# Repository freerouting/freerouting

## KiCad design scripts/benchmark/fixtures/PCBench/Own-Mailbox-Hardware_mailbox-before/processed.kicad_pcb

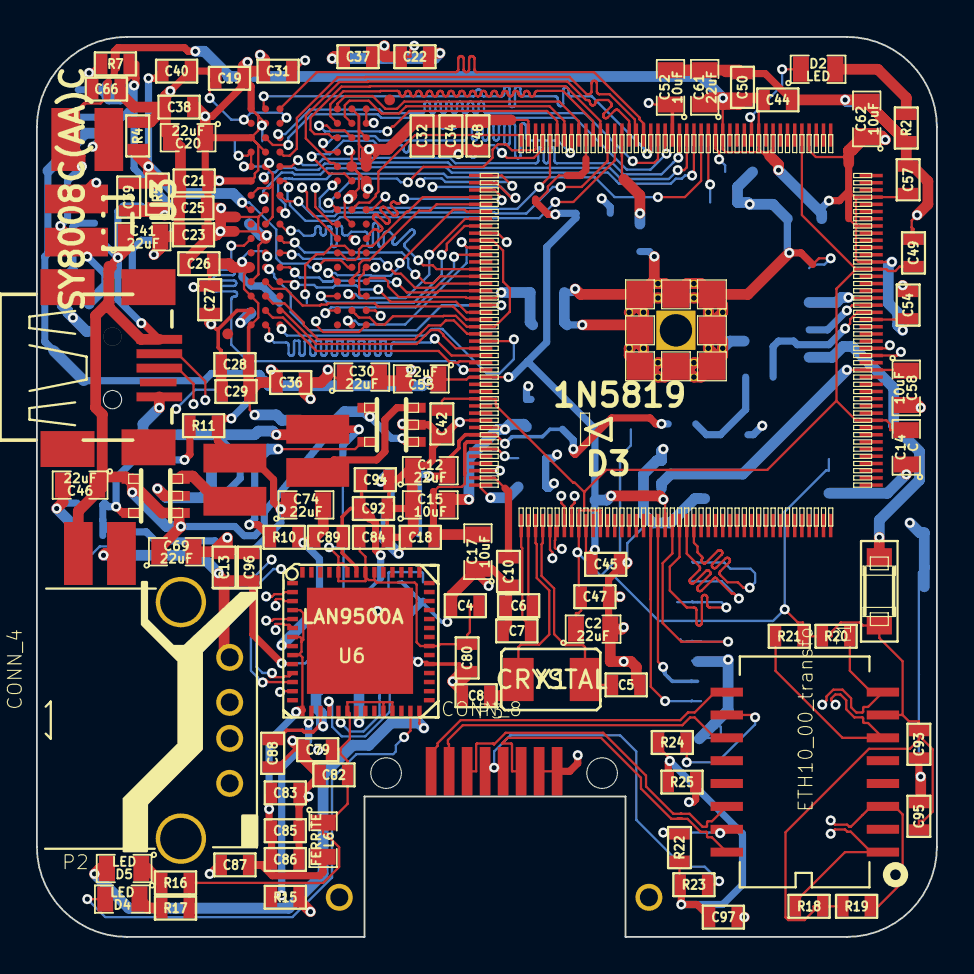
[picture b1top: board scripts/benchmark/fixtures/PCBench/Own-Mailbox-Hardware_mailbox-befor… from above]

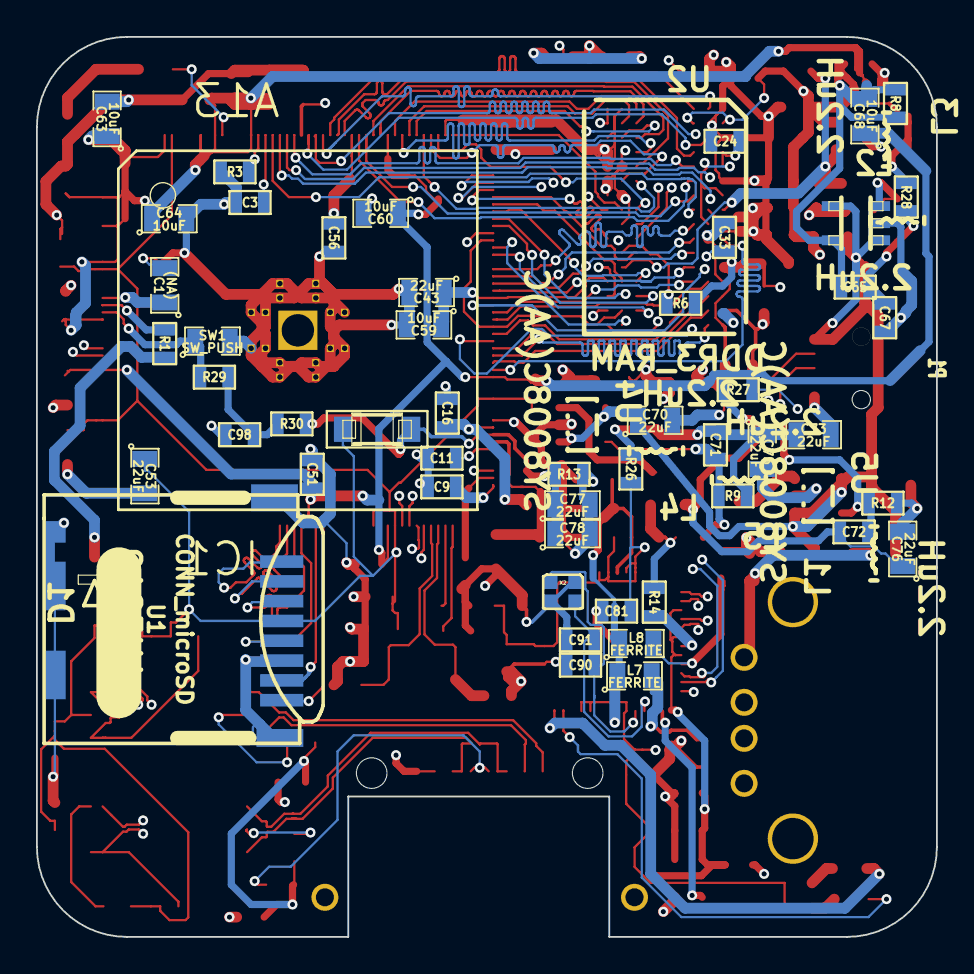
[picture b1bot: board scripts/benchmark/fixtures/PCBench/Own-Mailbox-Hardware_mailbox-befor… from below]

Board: 4 copper layers, 50.0 x 50.0 mm, 154 parts (50 on the bottom side), 74 nets.

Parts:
C1: (NA); SM0805
C2, C12, C20, C30, C41, C43, C46, C53, C55, C61, C69, C70, C73, C74, C75, C76, C77, C78: 22uF; SM0805
C3, C4, C13, C16, C18, C19, C21, C23, C24, C25, C26, C27, C28, C29, C31, C32, C33, C34, C36, C37, C38, C39, C40, C42, C44, C45, C47, C48, C49, C50, C51, C54, C56, C57, C79, C80, C81, C82, C83, C84, C85, C86, C87, C88, C92, C93, C94, C95, C96: 100nF; SM0603
C5, C8, C90, C91: 10pF; SM0603
C6, C7, C9, C10, C22, C98: 1nF; SM0603
C11, C89, C97: 1uF; SM0603
C14: C; SM0805
C15, C17, C52, C58, C59, C60, C62, C63, C64, C68: 10uF; SM0805
C65, C72: 22pF; SM0603
C66, C67: 22uF; SM0603
C71: 47pF; SM0603
D1, D3: 1N5819; SOD-123
D2, D4, D5: LED; SM0805
IC1: A13; TQFP176
L1, L2, L3, L4, L5: 2.2uH; CD32
L6, L7, L8: FERRITE; SM0805
P1: CONN_4; CONN_USB_MINI_PIERRE
P2: CONN_4; USB-A_TH
P3: CONN_8; RJ45_LP_RA_SMT
R1: 47k; SM0603
R2: 500R; SM0603
R3: 240R; SM0603
R4, R5: 1k(1%); SM0603
R6: 240R(1%); SM0603
R7: 2k(1%); SM0603
R8: 1.5k(1%); SM0603
R9: 100k(1%); SM0603
R10: 22k(1%); SM0603
R11: 4.99k(1%); SM0603
R12: 3.3k(1%); SM0603
R13: 2.2k; SM0603
R14, R15: R; SM0603
R16, R17: 100R; SM0603
R18, R19, R20, R21: 50R; SM0603
R22, R23, R24, R25: 75R; SM0603
R26, R27, R28: 0R; SM0603
R29: 6.8k(1%); SM0603
R30: 100k (1%); SM0603
SW1: SW_PUSH; SM0805
T1: ETH10_00_transfo; H1601CG
U1: CONN_microSD; Memory_Card_microSD_DM3CS-SF
U2: DDR3_RAM; FBGA96
U3, U4, U5: SY8008C(AA)C; SOT23-5
U6: LAN9500A; QFN48
X1: CRYSTAL; SMDXTAL24mhz
X2: CRYSTAL_SMD2; Xtal25Mhz

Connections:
1V5: C19.1, C20.1, C21.1, C23.1, C24.1, C25.1, C26.1, C27.1, C28.1, C29.1, C30.1, C31.1, C32.1, C33.1, C34.1, C36.1, C37.1, C38.1, C39.1, C43.1, C48.1, C52.1, C56.1, C59.1, IC1.23, IC1.30, IC1.43, IC1.53, IC1.62, R5.1, R27.1, U2.A1, U2.A8, U2.B2, U2.C1, U2.C9, U2.D2, U2.D9, U2.E9, U2.F1, U2.H2, U2.H9, U2.K2, U2.K8, U2.N1, U2.N9, U2.R1, U2.R9
3VA: C12.2, C77.1, C78.1, D3.2, IC1.81, R13.1, R30.1
+5V: C41.1, C46.1, C69.1, C70.1, L1.2, P1.1, U3.1, U3.4, U4.1, U4.4, U5.1, U5.4
/Erhernet/RX+: P3.7, T1.11
/Erhernet/RX-: P3.8, T1.9
/Erhernet/TX+: P3.3, T1.16
/Erhernet/TX-: P3.6, T1.14
LED1: D4.2, U6.27
LED2: D5.2, U6.28
unnamed: C1.1, IC1.159
unnamed: C3.1, IC1.18
unnamed: C6.2, IC1.90
unnamed: C7.2, IC1.89
unnamed: C9.2, IC1.88
unnamed: C10.2, IC1.87
unnamed: C11.2, IC1.83
unnamed: C13.1, L1.1, P2.1
unnamed: C15.2, C16.2, IC1.80
unnamed: C17.2, C18.2, IC1.82
unnamed: C22.2, IC1.86
unnamed: C39.2, C40.1, R4.1, R5.2, U2.H1, U2.M8
unnamed: C65.1, C66.1, C67.1, L2.2, R7.1, R28.2
unnamed: C71.1, C73.1, C75.1, L4.2, R9.1, R26.2
unnamed: C71.2, R9.2, R10.1, U4.5
unnamed: C72.1, C74.1, C76.1, L5.2, R11.1, R27.2
unnamed: C72.2, R11.2, R12.1, U5.5
unnamed: C90.2, U6.19, X2.3
unnamed: C91.2, U6.18, X2.1
unnamed: C97.2, R22.1, R23.1, R24.1, R25.1
unnamed: C98.1, R29.1, R30.2
unnamed: D1.2, R1.1
unnamed: D2.1, IC1.12
unnamed: D2.2, R2.1
unnamed: D4.1, R17.1
unnamed: D5.1, R16.1
unnamed: IC1.17, R3.1
unnamed: IC1.158, R1.2
unnamed: L2.1, U3.3
unnamed: L4.1, U4.3
unnamed: L5.1, U5.3
unnamed: P3.1, P3.2, R25.2
unnamed: P3.4, P3.5, R23.2
unnamed: R6.1, U2.L8
unnamed: R14.2, U6.8
unnamed: R15.2, U6.16
unnamed: R22.2, T1.15
unnamed: R24.2, T1.10
RPX_N: R20.1, T1.8, U6.5
RPX_P: R21.1, T1.6, U6.6
SDC0_CLK: IC1.110, U1.5
SDC0_CMD: IC1.111, U1.3
SDC0_D0: IC1.108, U1.7
SDC0_D1: IC1.107, U1.8
SDC0_D2: IC1.113, U1.1
SDC0_D3: IC1.112, U1.2
SVREF: C1.2, C2.2, C3.2, C4.1, C5.1, C6.1, C7.1, C8.1, C9.1, C10.1, C11.1, C12.1, C13.2, C14.1, C15.1, C16.1, C17.1, C18.1, C19.2, C20.2, C21.2, C22.1, C23.2, C24.2, C25.2, C26.2, C27.2, C28.2, C29.2, C30.2, C31.2, C32.2, C33.2, C34.2, C36.2, C37.2, C38.2, C40.2, C41.2, C42.2, C43.2, C44.2, C45.2, C46.2, C47.2, C48.2, C49.2, C50.2, C51.2, C52.2, C53.2, C54.2, C55.2, C56.2, C57.2, C58.2, C59.2, C60.2, C61.2, C62.2, C63.2, C64.2, C65.2, C66.2, C67.2, C68.2, C69.2, C70.2, C73.2, C74.2, C75.2, C76.2, C77.2, C78.2, C79.2, C80.2, C81.2, C82.2, C83.2, C84.2, C85.2, C86.2, C87.2, C88.2, C89.2, C90.1, C91.1, C92.2, C93.1, C94.2, C95.2, C96.2, C97.1, C98.2, IC1.79, IC1.177, P1.4, P2.4, R2.2, R3.2, R4.2, R6.2, R7.2, R8.1, R8.2, R10.2, R12.2, R13.2, R14.1, R15.1, SW1.2, U1.6, U1.9, U2.A9, U2.B1, U2.B3, U2.B9, U2.D1, U2.D8, U2.E1, U2.E2, U2.E8, U2.F9, U2.G1, U2.G8, U2.G9, U2.J2, U2.J8, U2.L2, U2.M1, U2.M9, U2.P1, U2.P9, U2.T1, U2.T9, U3.2, U3.5, U4.2, U5.2, U6.13, U6.33, X2.2, X2.4
TPX_N: R19.2, T1.3, U6.2
TPX_P: R18.2, T1.1, U6.3
UART1_RX: IC1.151, P1.3
UART1_TX: IC1.152, P1.2
UBOOT: IC1.157, R29.2, SW1.1
USB_ETH_N: IC1.93, U6.11
USB_ETH_P: IC1.94, U6.12
USB_HOST_N: IC1.95, P2.2
USB_HOST_P: IC1.96, P2.3
VCC: C2.1, C4.2, C14.2, C42.1, C47.1, C49.1, C53.1, C79.1, C80.1, C81.1, C82.1, C84.1, C93.2, C95.1, D1.1, D3.1, IC1.5, IC1.76, IC1.97, IC1.100, IC1.142, IC1.163, L6.1, R16.2, R17.2, R18.1, R19.1, R20.2, R21.2, R26.1, T1.7, U1.4, U6.20, U6.24, U6.25, U6.35, U6.48, U6.49, U6.51, U6.52
VDD33A: C83.1, C85.1, C86.1, C87.1, L6.2, U6.4, U6.7, U6.9, U6.15
VDDBUSPLL: C88.1, L7.2, U6.17
VDDCORE: C89.1, C92.1, C94.1, L7.1, L8.1, U6.21, U6.50
VDDPLL: C96.1, L8.2, U6.10
VDD_CPU: C44.1, C50.1, C54.1, C57.1, C61.1, C62.1, C63.1, C64.1, IC1.4, IC1.9, IC1.11, IC1.16, IC1.156, IC1.164, IC1.169, IC1.173, L3.1, R28.1
VDD_INT: C45.1, C51.1, C55.1, C58.1, C60.1, C68.1, IC1.35, IC1.73, IC1.98, IC1.109, IC1.149, L3.2
X1_N: C5.2, IC1.92, X1.1
X1_P: C8.2, IC1.91, X1.2

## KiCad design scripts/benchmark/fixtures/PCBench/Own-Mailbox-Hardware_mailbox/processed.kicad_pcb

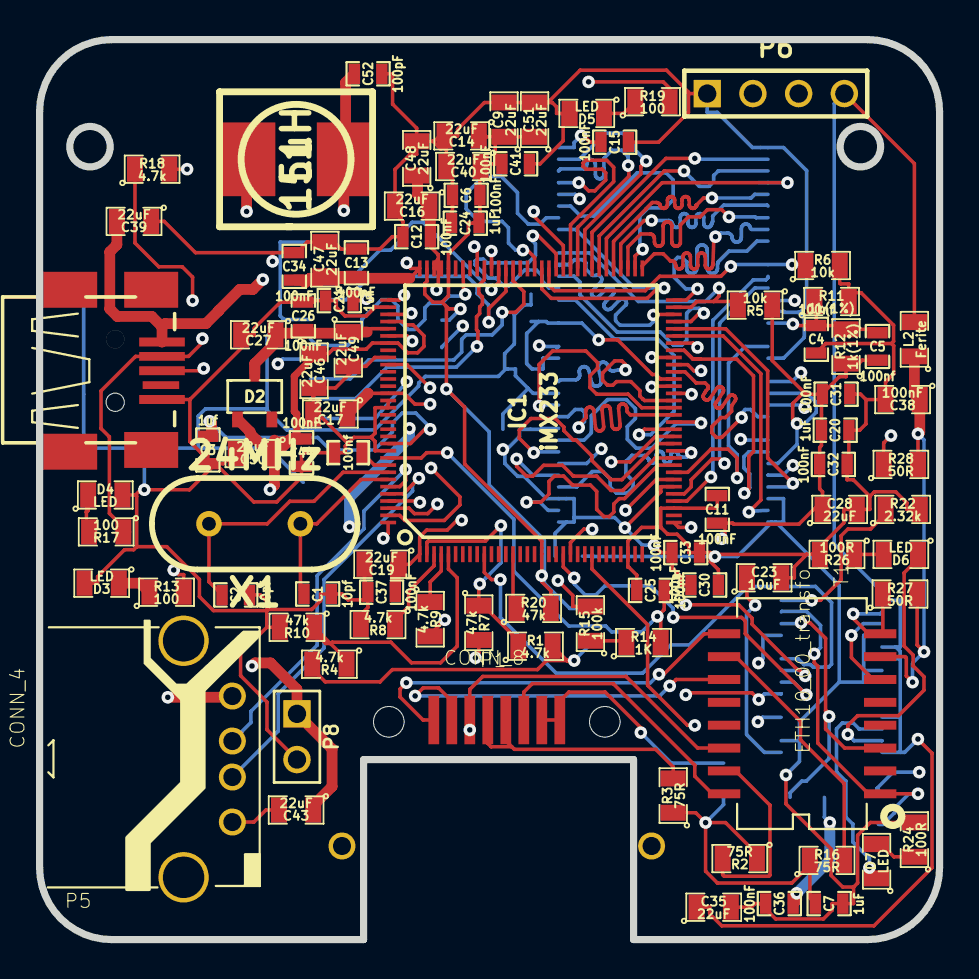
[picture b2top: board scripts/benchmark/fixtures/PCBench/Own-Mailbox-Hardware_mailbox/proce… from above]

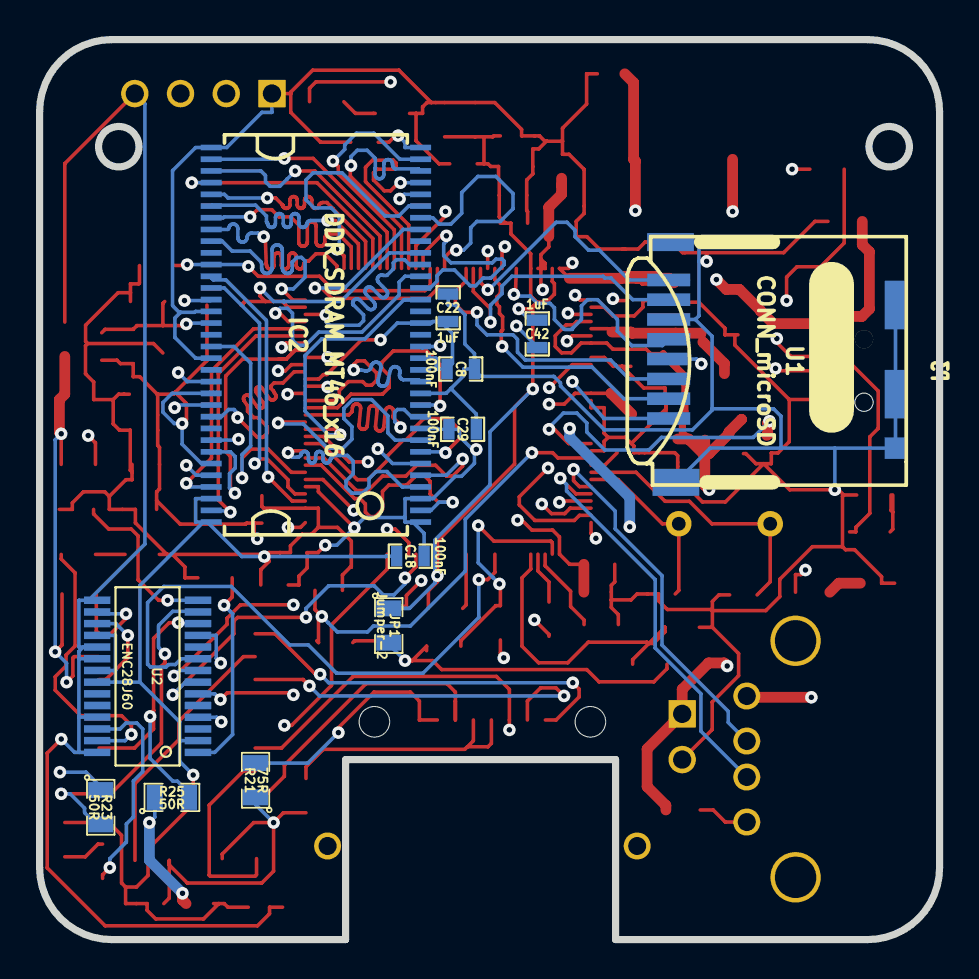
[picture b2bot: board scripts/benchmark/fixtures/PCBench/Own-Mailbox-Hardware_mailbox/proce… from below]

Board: 4 copper layers, 50.0 x 50.0 mm, 99 parts (12 on the bottom side), 107 nets.

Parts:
C1, C2: 10pf; SM0603_Capa
C3: 1uf; SM0603_Capa
C4, C5: 100nf; SM0603_Capa
C6, C8, C11, C12, C13, C15, C18, C25, C26, C29, C30, C31, C32, C33, C34, C36, C37, C41, C44: 100nF; SM0603_Capa
C7, C20, C21, C22, C24, C42: 1uF; SM0603_Capa
C9, C14, C16, C17, C19, C27, C28, C35, C39, C40, C43, C46, C47, C48, C49, C50, C51: 22uF; SM0805
C10: 100nf; SM0603_Opendous
C23: 10uF; SM0805
C38: 100nF; SM0805
C52: 100pF; SM0603_Capa
D2: D_schottky; SOT23-3_Opendous
D3, D4, D5, D6, D7: LED; SM0805
IC1: iMX233; LQFP128_14x14mm_0.4mmPitch_iMX233
IC2: DDR_SDRAM_MT46_x16; TSOP66_JEDEC_DDR_SDRAM
JP1: Jumper-2; SM0805
L1: 15uH; inductor22
L2: Ferite; SM0805
P1: CONN_8; RJ45_LP_RA_SMT
P3: CONN_4; CONN_USB_MINI_PIERRE
P5: CONN_4; USB-A_TH
P6: CONN_4; PIN_ARRAY_4x1
P8: CONN_2; PIN_ARRAY_2X1
R1, R4, R8, R9, R18: 4.7k; SM0805
R2, R3, R16, R21: 75R; SM0805
R5, R6: 10k; SM0805
R7, R10, R20: 47k; SM0805
R11, R12: 1k(1%); SM0805
R13, R17, R19: 100; SM0805
R14: 1K; SM0805
R15: 100k; SM0805
R22: 2.32k; SM0805
R23, R25, R27, R28: 50R; SM0805
R24, R26: 100R; SM0805
T1: ETH10_00_transfo; H1601CG
U1: CONN_microSD; Memory_Card_microSD_DM3CS-SF
U2: ENC28J60; tssop-28
X1: 24MHz; HC-49V

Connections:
5VOUT: C21.1, C39.2, IC1.102, P3.1, P5.1
+2.5V: C5.1, C8.1, C11.1, C15.1, C18.1, C20.1, C22.1, C28.1, C29.1, C30.1, C31.1, C32.1, C33.1, IC1.38, IC1.45, IC1.53, IC1.106, IC2.1, IC2.3, IC2.9, IC2.15, IC2.18, IC2.33, IC2.55, IC2.61, R5.1, R12.1
+3.3V: C6.1, C9.1, C14.1, C24.1, C35.1, C40.1, C41.1, C42.1, C51.1, IC1.18, IC1.92, IC1.95, JP1.1, L2.2, P6.4, R13.2, R18.2, R20.2, U1.4, U2.15, U2.19, U2.20, U2.25, U2.28
/Ethernet/RX+: P1.7, T1.11
/Ethernet/RX-: P1.8, T1.9
/Ethernet/TX+: P1.3, T1.16
/Ethernet/TX-: P1.6, T1.14
/LCD_D0: IC1.2, R1.1, R7.1
/LCD_D1: IC1.3, R8.1
/LCD_D2: IC1.4, R9.1
/LCD_D3: IC1.5, R4.1, R10.1
/LCD_RS: IC1.14, R20.1
/SD_CLOCK: IC1.90, U1.5
/SD_CMD: IC1.83, U1.3
/UART2_RX: IC1.128, P6.3
/UART2_TX: IC1.127, P6.2
/U_RX: IC1.125, P3.3, R18.1
/U_TX: IC1.126, P3.2, R17.1
DDRA0: IC1.76, IC2.29
DDRA1: IC1.75, IC2.30
DDRA2: IC1.74, IC2.31
DDRA3: IC1.73, IC2.32
DDRA4: IC1.72, IC2.35
DDRA5: IC1.71, IC2.36
DDRA6: IC1.70, IC2.37
DDRA7: IC1.69, IC2.38
DDRA8: IC1.68, IC2.39
DDRA9: IC1.67, IC2.40
DDRA10: IC1.66, IC2.28
DDRA11: IC1.65, IC2.41
DDRA12: IC1.64, IC2.42
DDR_BA0: IC1.79, IC2.26
DDR_BA1: IC1.80, IC2.27
DDR_CAS: IC1.61, IC2.22
DDR_CE0n: IC1.63, IC2.24, R5.2
DDR_CKE: IC1.78, IC2.44, R6.1
DDR_CLK: IC1.36, IC2.45
DDR_CLKn: IC1.37, IC2.46
DDR_DO0: IC1.41, IC2.2
DDR_DO1: IC1.43, IC2.4
DDR_DO2: IC1.42, IC2.5
DDR_DO3: IC1.44, IC2.7
DDR_DO4: IC1.47, IC2.8
DDR_DO5: IC1.48, IC2.10
DDR_DO6: IC1.49, IC2.11
DDR_DO7: IC1.50, IC2.13
DDR_DO8: IC1.51, IC2.54
DDR_DO9: IC1.52, IC2.56
DDR_DO10: IC1.54, IC2.57
DDR_DO11: IC1.55, IC2.59
DDR_DO12: IC1.57, IC2.60
DDR_DO13: IC1.58, IC2.62
DDR_DO14: IC1.60, IC2.63
DDR_DO15: IC1.59, IC2.65
DDR_DQM0: IC1.46, IC2.20
DDR_DQM1: IC1.56, IC2.47
DDR_DQS0: IC1.39, IC2.16
DDR_DQS1: IC1.40, IC2.51
DDR_RAS: IC1.62, IC2.23
DDR_WEn: IC1.77, IC2.21
GND: C1.1, C2.1, C3.2, C4.2, C6.2, C7.1, C8.2, C9.2, C10.2, C11.2, C12.2, C13.2, C14.2, C15.2, C16.2, C17.2, C18.2, C19.2, C20.2, C21.2, C22.2, C23.2, C24.2, C25.2, C26.2, C27.2, C28.2, C29.2, C30.2, C31.2, C32.2, C33.2, C34.2, C35.2, C36.1, C37.2, C38.2, C39.1, C40.2, C41.2, C42.2, C43.2, C44.2, C46.2, C47.2, C48.2, C49.2, C50.2, C51.2, C52.1, D3.2, D4.2, D5.2, IC1.30, IC1.35, IC1.98, IC1.105, IC1.111, IC1.112, IC1.118, IC2.6, IC2.12, IC2.34, IC2.48, IC2.52, IC2.64, IC2.66, P3.4, P5.4, P6.1, P8.2, R6.2, R7.2, R8.2, R9.2, R10.2, R11.2, R15.2, R22.2, R24.2, R26.2, U1.6, U1.9, U2.2, U2.11, U2.18, U2.21, U2.22
unnamed: C3.1, IC1.117
unnamed: C4.1, C5.2, IC2.49, R11.1, R12.2
unnamed: C7.2, R2.1, R3.1, R16.1, R21.1
unnamed: C23.1, U2.1
unnamed: C36.2, R23.1, R25.1
unnamed: C38.1, L2.1, R27.2, R28.2, T1.7
unnamed: C52.2, IC1.99, L1.2
unnamed: D3.1, R13.1
unnamed: D4.1, R17.2
unnamed: D5.1, R19.1
unnamed: D6.1, U2.27
unnamed: D6.2, R26.1
unnamed: D7.1, U2.26
unnamed: D7.2, R24.1
unnamed: IC1.84, U1.7
unnamed: IC1.85, U1.8
unnamed: IC1.86, U1.1
unnamed: IC1.87, U1.2
unnamed: IC1.88, R19.2
unnamed: IC1.97, L1.1
unnamed: IC1.123, P5.2
unnamed: IC1.124, P5.3
unnamed: JP1.2, R1.2, R4.2
unnamed: P1.1, P1.2, R21.2
unnamed: P1.4, P1.5, R3.2
unnamed: R2.2, T1.15
unnamed: R14.1, R15.1
unnamed: R16.2, T1.10
unnamed: R22.1, U2.14
unnamed: R23.2, T1.1, U2.13
unnamed: R25.2, T1.3, U2.12
unnamed: R27.1, T1.8, U2.16
unnamed: R28.1, T1.6, U2.17
PSWITCH: C25.1, IC1.119, R14.2
SPI_CS: IC1.10, U2.9
SPI_INT: IC1.25, U2.4
SPI_MISO: IC1.22, U2.6
SPI_MOSI: IC1.21, U2.7
SPI_SCK: IC1.33, U2.8
VDD4P2: C26.1, C27.1, C49.1, D2.2, IC1.101
VDDA: C13.1, C17.1, C34.1, C47.1, IC1.96, IC1.110
VDDD: C12.1, C16.1, C19.1, C37.1, C48.1, IC1.1, IC1.93, IC1.94
VDD_BATT: C43.1, C44.1, C46.1, C50.1, D2.1, IC1.100, IC1.103, P8.1
VDD_XTAL: C10.1, IC1.120
XTALI: C1.2, IC1.122, X1.1
XTALO: C2.2, IC1.121, X1.2

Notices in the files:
scripts/benchmark/fixtures/PCBench/Own-Mailbox-Hardware_mailbox/processed.kicad_pcb:
CopyRight Pierre Parent & Ael gain
this is open hardware you may redistribute it under the cern open harware  license 1.3
parts and their libraries:
Copyright © 2012, Michel Stempin, All rights reserved
Licenced under Creative Commons CC BY-SA 3.0 license.
